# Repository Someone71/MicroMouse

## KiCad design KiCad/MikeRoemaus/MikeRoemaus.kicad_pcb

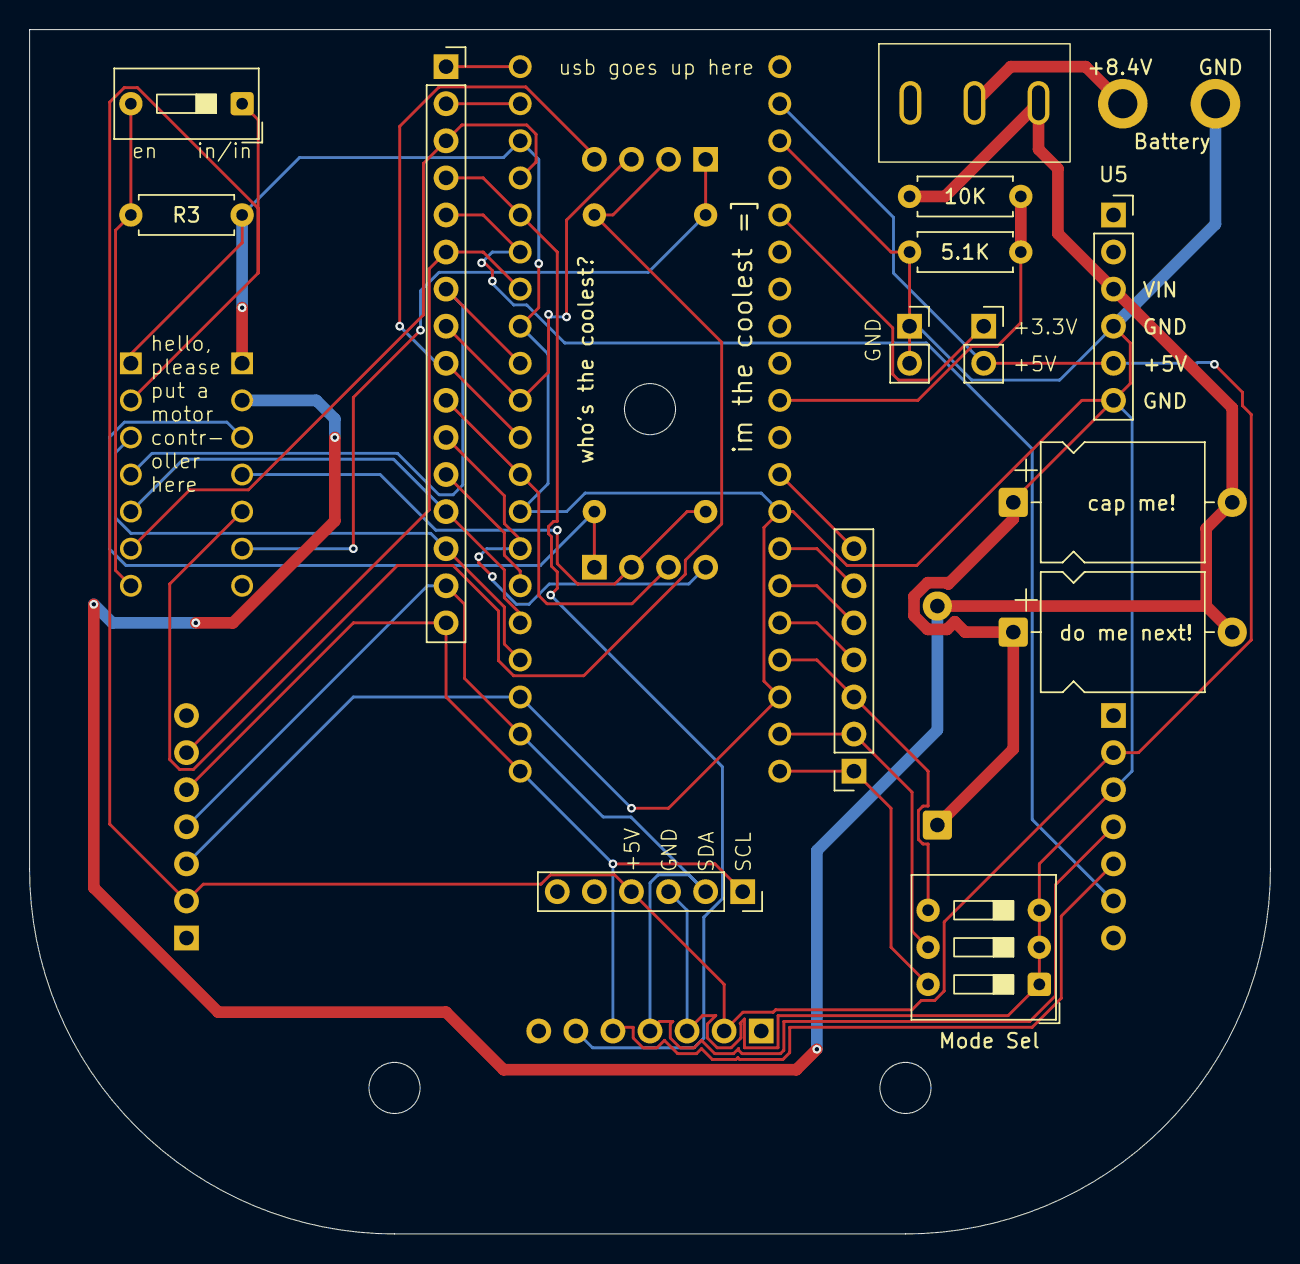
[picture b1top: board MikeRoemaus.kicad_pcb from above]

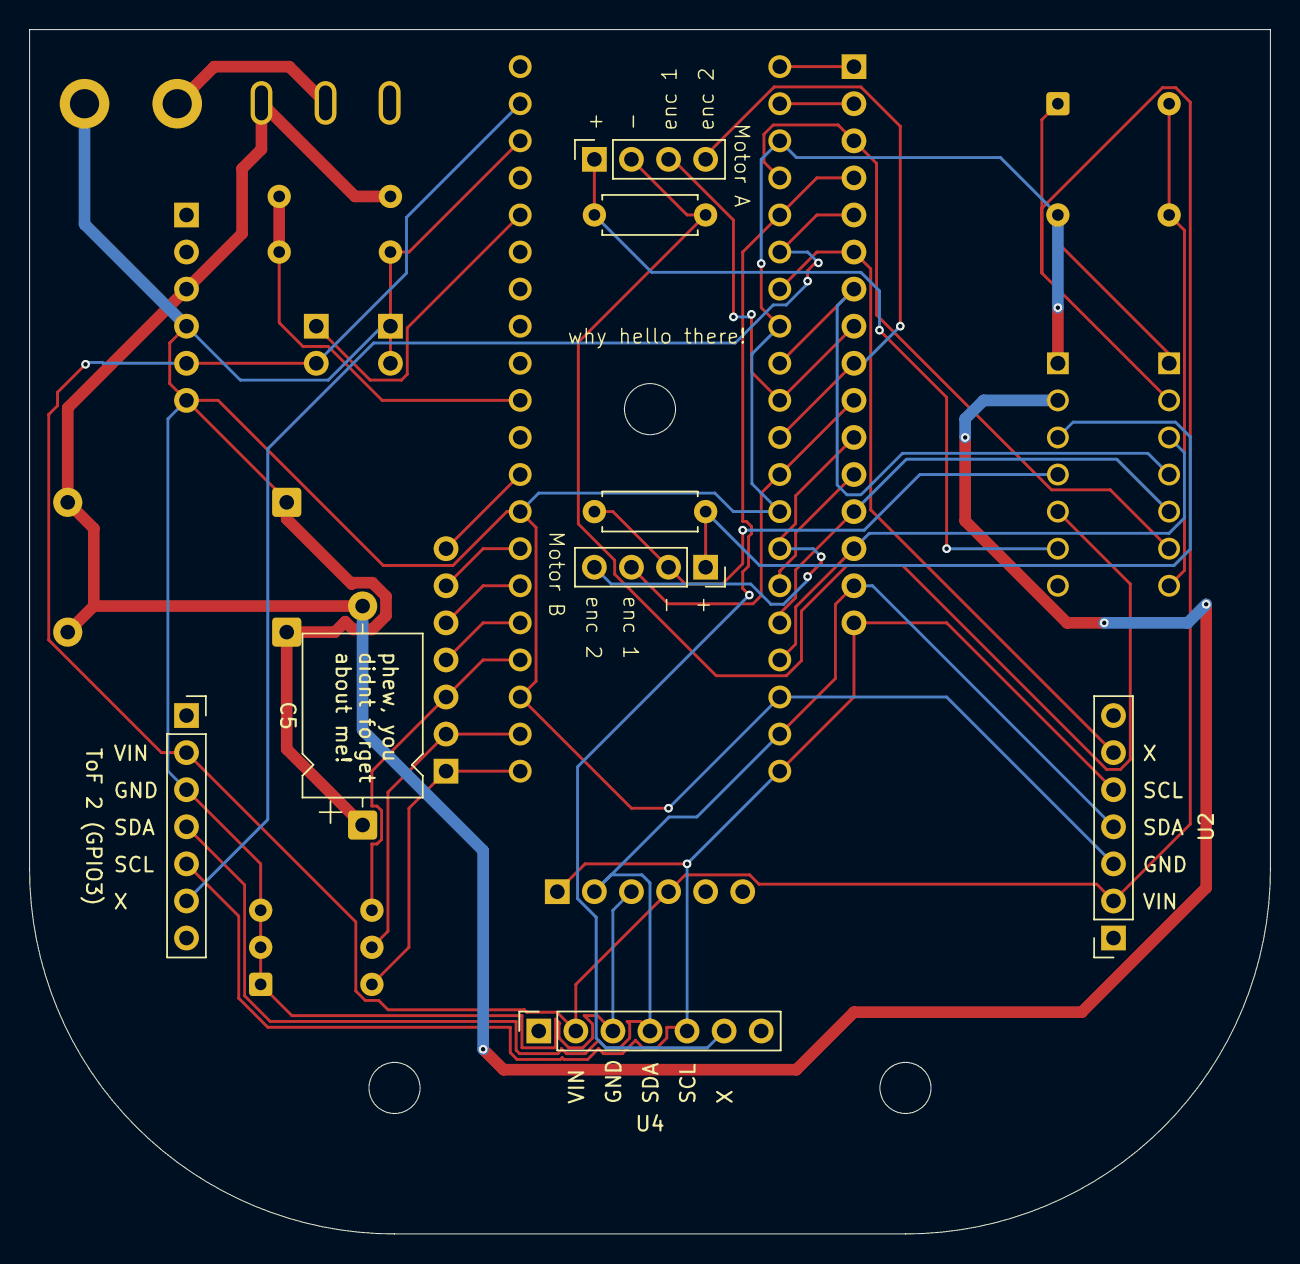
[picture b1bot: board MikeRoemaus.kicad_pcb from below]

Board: 2 copper layers, 85.0 x 82.5 mm, 28 parts (8 on the bottom side), 34 nets.

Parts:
A2: RaspberryPi_Pico_W; rpi_pico_w
C1, C2: C; R_Axial_DIN0207_L6.3mm_D2.5mm_P7.62mm_Horizontal
C3: 470uF; CP_Axial_L11.0mm_D8.0mm_P15.00mm_Horizontal
C4: 1uF; CP_Axial_L11.0mm_D8.0mm_P15.00mm_Horizontal
C5: 0.1uF; CP_Axial_L11.0mm_D8.0mm_P15.00mm_Horizontal
H2, H3, H4: MountingHole; MountingHole_3.5mm
J1, J2: Conn_01x04_Socket; PinSocket_1x04_P2.54mm_Vertical
J3: Conn_01x02_Socket; Battery
J4: Conn_01x16_Socket; PinSocket_1x16_P2.54mm_Vertical
J5: Conn_01x07_Socket; PinSocket_1x07_P2.54mm_Vertical
J6, J7: Conn_01x02_Socket; PinSocket_1x02_P2.54mm_Vertical
R1, R3: 10K; R_Axial_DIN0207_L6.3mm_D2.5mm_P7.62mm_Horizontal
R2: 5.1K; R_Axial_DIN0207_L6.3mm_D2.5mm_P7.62mm_Horizontal
SW1: SW_SPDT; pwr sw
SW2: SW_DIP_x03; SW_DIP_SPSTx03_Slide_9.78x9.8mm_W7.62mm_P2.54mm
SW3: SW_DIP_x01; SW_DIP_SPSTx01_Slide_9.78x4.72mm_W7.62mm_P2.54mm
U1, U5: PinSocket_1x06_P2.54mm_Vertical
U2, U3, U4: PinSocket_1x07_P2.54mm_Vertical
U6: DRV8835_Dual_Motor_Driver_Carrier

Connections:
+3.3V: A2.36 (3V3), J7.1
+5V: A2.39 (VSYS), J7.2, SW3.1, U1.4 (VIN), U2.2 (VIN), U3.2 (VIN), U4.2 (VIN), U5.5 (VOUT), U6.2 (VCC)
/BAT + for motors: C3.2, C4.2, C5.2, R1.1, SW1.3 (C), U5.3 (VIN), U6.13 (VIN)
/ToF 1: A2.5 (GPIO3), J4.4, U4.6 (XSHUT)
/ToF 2: A2.6 (GPIO4), J4.5, U3.6 (XSHUT)
/ToF 3: A2.7 (GPIO5), J4.6, U2.6 (XSHUT)
/battery reader: A2.31 (GPIO26_ADC0), R1.2, R2.1
/mode sel 1: A2.21 (GPIO16), J5.1, SW2.6
/mode sel 2: A2.22 (GPIO17), J5.2, SW2.5
/mode sel 4: A2.24 (GPIO18), J5.3, SW2.4
/motor A +out: C1.1, J1.1, U6.9 (AOUT1)
/motor A -out: C1.2, J1.2, U6.10 (AOUT2)
/motor A enc 1: A2.10 (GPIO7), J1.3, J4.8
/motor A enc 2: A2.11 (GPIO8), J1.4, J4.9
/motor A pwm: A2.16 (GPIO12), J4.13, U6.5 (AIN2/AENABLE)
/motor A selector: A2.4 (GPIO2), J4.3, U6.6 (AIN1/APHASE)
/motor B +out: C2.1, J2.1, U6.12 (BOUT2)
/motor B -out: C2.2, J2.2, U6.11 (BOUT1)
/motor B enc 1: A2.12 (GPIO9), J2.3, J4.10
/motor B enc 2: A2.14 (GPIO10), J2.4, J4.11
/motor B pwm: A2.17 (GPIO13), J4.14, U6.3 (BIN2/BENABLE)
/motor B selector: A2.9 (GPIO6), J4.7, U6.4 (BIN1/BPHASE)
/scl: A2.20 (GPIO15), J4.16, U1.1 (SCL), U2.5 (SCL), U3.5 (SCL), U4.5 (SCL)
/sda: A2.19 (GPIO14), J4.15, U1.2 (SDA), U2.4 (SDA), U3.4 (SDA), U4.4 (SDA)
GND: A2.3 (GND), A2.8 (GND), A2.13 (GND), A2.18 (GND), A2.23 (GND), A2.28 (GND), A2.38 (GND), C3.1, C4.1, C5.1, J3.2, J6.1, J6.2, R2.2, R3.1, SW2.1, SW2.2, SW2.3, U1.3 (GND), U2.3 (GND), U3.3 (GND), U4.3 (GND), U5.4 (GND), U5.6 (GND), U6.1 (GND), U6.14 (GND)
unnamed: A2.1 (GPIO0), J4.1
unnamed: A2.2 (GPIO1), J4.2
unnamed: A2.15 (GPIO11), J4.12
unnamed: A2.25 (GPIO19), J5.4
unnamed: A2.26 (GPIO20), J5.5
unnamed: A2.27 (GPIO21), J5.6
unnamed: A2.29 (GPIO22), J5.7
unnamed: J3.1, SW1.2 (B)
unnamed: R3.2, SW3.2, U6.7 (MODE)

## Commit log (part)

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2026-01-20 Update MicromouseCode.py
    added variable turn function
2026-06-30 Tuning for PIDF
    Updated PID constants for motor control and adjusted target encoder values for movement. Improved wall detection and pathfinding logic.
2026-06-30 Added PIDF
